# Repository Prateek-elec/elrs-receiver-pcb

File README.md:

# ELRS Receiver PCB (ESP8285 + SX1280) 📡

A compact **ExpressLRS (ELRS) receiver hardware design** built around **ESP8285** and the **SX1280** LoRa transceiver.
This repository contains the full **KiCad schematic and PCB layout**, along with documentation and renders.

---

## ✅ Features
- **ESP8285 MCU** (WiFi-enabled microcontroller, ELRS compatible)
- **SX1280 LoRa transceiver** for 2.4GHz ELRS
- **3.3V LDO regulation** using **MIC5219-3.3YMS**
- **Reverse polarity / input protection** using Schottky diode
- **RF output via coax / U.FL connector** support
- Status LED + reset/boot support
- Compact 2-layer PCB layout suitable for UAV / RC applications

---

## 🧩 Block Overview
### 1) MCU Section (ESP8285)
- Powered from 3.3V rail
- Boot/enable circuitry included
- UART pads/testpoints for debugging and flashing

### 2) RF Section (SX1280)
- SPI interface from ESP8285 (MISO/MOSI/SCK/CS)
- Reset and BUSY signals connected
- RF output routed to coax connector
- 52 MHz reference crystal provided

### 3) Power Section
- Input → Schottky protection → **MIC5219 3.3V LDO**
- Local decoupling capacitors placed close to ICs

---

## 📷 Project Preview
> Add your images in `docs/images/` and they will show here.

### Schematic

### PCB Layout

---

## 📂 Repository Structure
- `hardware/kicad/` → KiCad project files (`.kicad_pro`, `.kicad_sch`, `.kicad_pcb`)
- `docs/images/` → screenshots (schematic / PCB / 3D view)
- `fabrication/` → Gerbers, drill files, BOM, pick & place (optional)

---

## ✅ Getting Started (KiCad)
1. Install **KiCad 8 / KiCad 9**
2. Open the project file:
   - `hardware/kicad/elrs_receiver.kicad_pro`
3. View schematic:
   - `elrs_receiver.kicad_sch`
4. View PCB:
   - `elrs_receiver.kicad_pcb`
5. Export Gerbers (if needed):
   - PCB Editor → **File → Plot…**

---

## ⚠️ Notes / Disclaimer
This is a personal hardware project made for learning and experimentation.  
Please validate your RF layout, matching network, and manufacturing constraints before using it in real flight systems.

---

## 👤 Author
**Prateek Sarkar**  
Embedded Systems • PCB Design (KiCad) • UAV / Robotics

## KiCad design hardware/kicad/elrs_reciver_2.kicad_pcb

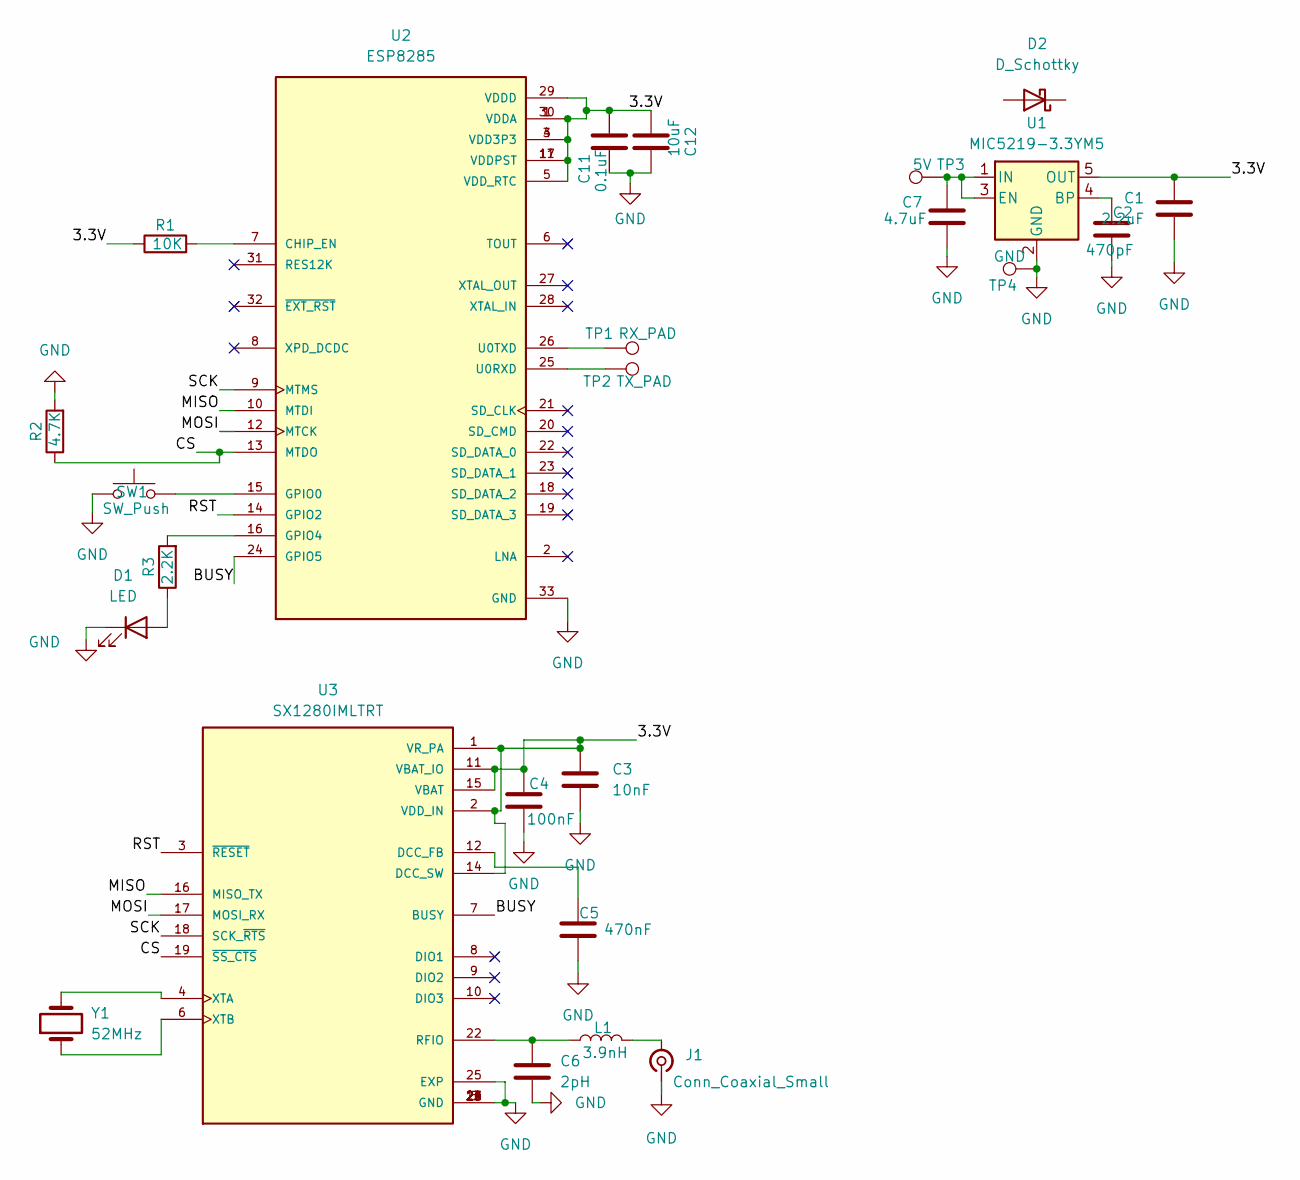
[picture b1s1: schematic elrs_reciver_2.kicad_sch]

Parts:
C1: 2.2uF; C_0201_0603Metric
C2: 470pF; C_0402_1005Metric
C3: 10nF; C_0402_1005Metric
C4: 100nF; C_0201_0603Metric
C5: 470nF; C_0402_1005Metric
C6: 2pH; C_0402_1005Metric
C7: 4.7uF; C_0201_0603Metric
C11: 0.1uF; C_0402_1005Metric
C12: 10uF; C_0201_0603Metric
D1: LED; LED_0201_0603Metric
D2: D_Schottky
J1: Conn_Coaxial_Small; U.FL_Hirose_U.FL-R-SMT-1_Vertical
L1: 3.9nH; L_0402_1005Metric
R1: 10K; R_0402_1005Metric
R2: 4.7K; R_0402_1005Metric
R3: 2.2K; R_0402_1005Metric
SW1: SW_Push; SW_Push_SPST_NO_Alps_SKRK
TP1: RX_PAD; TestPoint_Pad_1.5x1.5mm
TP2: TX_PAD; TestPoint_Pad_1.5x1.5mm
TP3: 5V; TestPoint_Pad_1.5x1.5mm
TP4: GND; TestPoint_Pad_1.5x1.5mm
U1: MIC5219-3.3YM5; SOT-23-5
U2: ESP8285; QFN-32-1EP_5x5mm_P0.5mm_EP3.7x3.7mm; PARTREV 2.0
U3: SX1280IMLTRT; QFN-24-1EP_4x4mm_P0.5mm_EP2.6x2.6mm; PARTREV 3.3
Y1: 52MHz; Crystal_SMD_3215-2Pin_3.2x1.5mm

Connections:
/3.3V: C1.1, C3.1, C4.1, C11.2, C12.1, R1.1, U1.5 (OUT), U2.1 (VDDA), U2.3 (VDD3P3), U2.4 (VDD3P3), U2.5 (VDD_RTC), U2.11 (VDDPST), U2.17 (VDDPST), U2.29 (VDDD), U2.30 (VDDA), U3.1 (VR_PA), U3.2 (VDD_IN), U3.11 (VBAT_IO), U3.14 (DCC_SW), U3.15 (VBAT)
/BUSY: U2.24 (GPIO5), U3.7 (BUSY)
/CS: R2.1, U2.13 (MTDO), U3.19 (~SS_CTS)
/MISO: U2.10 (MTDI), U3.16 (MISO_TX)
/MOSI: U2.12 (MTCK), U3.17 (MOSI_RX)
/RST: U2.14 (GPIO2), U3.3 (~RESET)
/SCK: U2.9 (MTMS), U3.18 (SCK_~RTS)
GND: C1.2, C2.2, C3.2, C4.2, C5.2, C6.2, C7.2, C11.1, C12.2, D1.1 (K), J1.1 (In), R2.2, SW1.1, TP4.1, U1.2 (GND), U2.33 (GND), U3.5 (GND), U3.13 (GND), U3.20 (GND), U3.21 (GND), U3.23 (GND), U3.24 (GND), U3.25 (EXP)
unnamed: D1.2 (A), R3.1
unnamed: J1.2 (Ext), L1.2
unnamed: C2.1, U1.4 (BP)
unnamed: C7.1, TP3.1, U1.1 (IN), U1.3 (EN)
unnamed: R1.2, U2.7 (CHIP_EN)
unnamed: SW1.2, U2.15 (GPIO0)
unnamed: R3.2, U2.16 (GPIO4)
unnamed: TP2.1, U2.25 (U0RXD)
unnamed: TP1.1, U2.26 (U0TXD)
unnamed: C5.1, U3.12 (DCC_FB)
unnamed: C6.1, L1.1, U3.22 (RFIO)
unnamed: U3.4 (XTA), Y1.2
unnamed: U3.6 (XTB), Y1.1

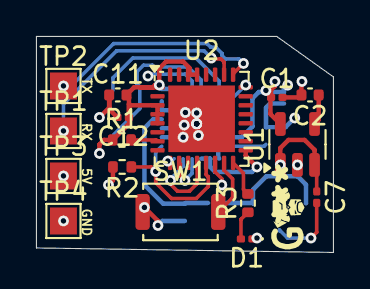
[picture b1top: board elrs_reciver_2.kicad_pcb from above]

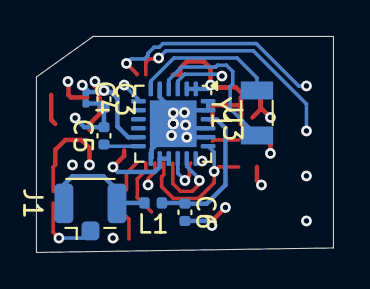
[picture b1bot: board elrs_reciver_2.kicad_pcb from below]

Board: 4 copper layers, 16.5 x 12.0 mm, 24 parts (8 on the bottom side), 21 nets.
